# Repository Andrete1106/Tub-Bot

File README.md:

# Proyecto Tub-Bot
Repositorio para el Proyecto "Tub-Bot" correspondiente a las materias de:
- Introducción a Ingeniería Electrónica 
- Taller de Electrónica

**Universidad Nacional de Colombia**

## **Integrantes**
- Andres David Hincapié Álvarez (Ingeniería Electrónica)  
- Samuel Alejandro Bulla Fiquitiva (Ingeniería Electrónica)
- Juan Jose Aleman Martinez (Ingeniería Electrónica)
- Camilo Andrés Triana Ortiz (Ingeniería Mecatrónica)
- Ricardo Javier Rivas Sabogal (Ingeniería Electrónica)
- Luis Armando Berrocal Estrada (Ingeniería Electrónica)

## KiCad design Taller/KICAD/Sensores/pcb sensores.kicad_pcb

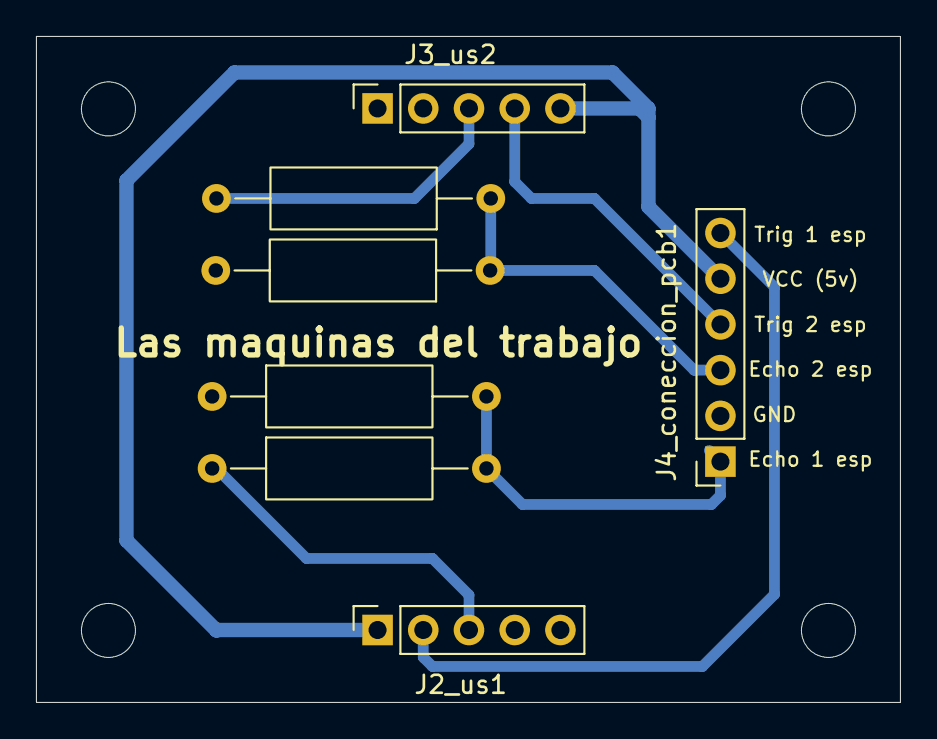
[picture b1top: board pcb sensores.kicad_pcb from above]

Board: 2 copper layers, 48.0 x 37.0 mm, 7 parts (0 on the bottom side), 8 nets.

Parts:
J2_us1, J3_us2: Conn_01x05; PinSocket_1x05_P2.54mm_Vertical
J4_coneccion_pcb1: Conn_01x06; PinSocket_1x06_P2.54mm_Vertical
R1, R4: 20 KOhm; R_Axial_DIN0309_L9.0mm_D3.2mm_P15.24mm_Horizontal
R2, R3: 10 KOhm; R_Axial_DIN0309_L9.0mm_D3.2mm_P15.24mm_Horizontal

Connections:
+5V: J2_us1.1 (vcc_us1), J3_us2.5 (vcc_us2), J4_coneccion_pcb1.5
/echo1_esp: J4_coneccion_pcb1.1, R1.2, R2.2
/echo2_esp: J4_coneccion_pcb1.3, R3.1, R4.1
/trig1_esp: J2_us1.2 (trig1_raw), J4_coneccion_pcb1.6
/trig2_esp: J3_us2.4 (trig2_raw), J4_coneccion_pcb1.4
GND: J2_us1.5 (GND_us1), J3_us2.1 (GND_us2), J4_coneccion_pcb1.2, R1.1, R4.2
unnamed: J2_us1.3 (echo1_raw), R2.1
unnamed: J3_us2.3 (echo2_raw), R3.2

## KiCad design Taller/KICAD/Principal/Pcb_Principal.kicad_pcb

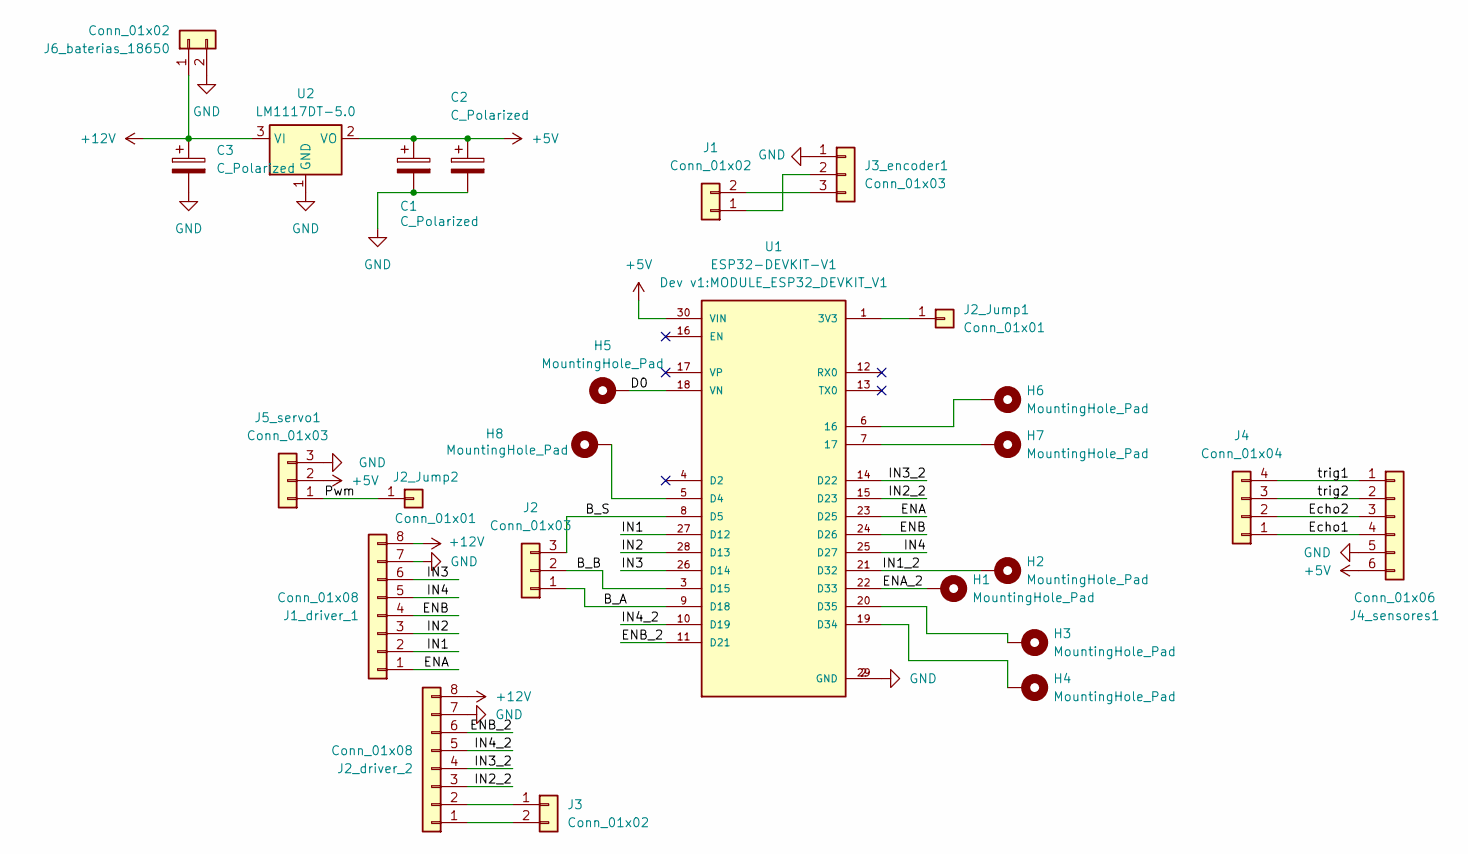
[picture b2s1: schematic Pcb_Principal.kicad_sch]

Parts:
C1, C2, C3: C_Polarized; CP_Radial_D5.0mm_P2.50mm
H1, H2, H3, H4, H5, H6, H7, H8: MountingHole_Pad; Pin_D1.0mm_L10.0mm
J1, J3: Conn_01x02; PinHeader_1x02_P2.54mm_Vertical
J1_driver_1, J2_driver_2: Conn_01x08; PinSocket_1x08_P2.54mm_Vertical
J2: Conn_01x03; PinHeader_1x03_P2.54mm_Vertical
J2_Jump1, J2_Jump2: Conn_01x01; PinHeader_1x01_P2.54mm_Vertical
J3_encoder1, J5_servo1: Conn_01x03; PinSocket_1x03_P2.54mm_Vertical
J4: Conn_01x04; PinHeader_1x04_P2.54mm_Vertical
J4_sensores1: Conn_01x06; PinSocket_1x06_P2.54mm_Vertical
J6_baterias_18650: Conn_01x02; PinSocket_1x02_P2.54mm_Vertical
U1: ESP32-DEVKIT-V1; MODULE_ESP32_DEVKIT_V1; PARTREV N/A
U2: LM1117DT-5.0; SIPAK_Vertical

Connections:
+5V: C1.1, C2.1, J4_sensores1.6 (s), J5_servo1.2, U1.30 (VIN), U2.2 (VO)
+12V: C3.1, J1_driver_1.8 (+12V), J2_driver_2.8 (+12V), J6_baterias_18650.1, U2.3 (VI)
/B_A: J2.1, U1.9 (D18)
/B_B: J2.2, U1.3 (D15)
/B_S: J2.3, U1.8 (D5)
/D0: H5.1, U1.18 (VN)
/ENA: J1_driver_1.1 (ENA), U1.23 (D25)
/ENA_2: H1.1, U1.22 (D33)
/ENB: J1_driver_1.4 (IN3), U1.24 (D26)
/ENB_2: J2_driver_2.6 (ENB), U1.11 (D21)
/Echo1: J4.1, J4_sensores1.4
/Echo2: J4.2, J4_sensores1.3
/IN1: J1_driver_1.2 (IN1), U1.27 (D12)
/IN1_2: H2.1, U1.21 (D32)
/IN2: J1_driver_1.3 (IN2), U1.28 (D13)
/IN2_2: J2_driver_2.3 (IN2_2), U1.15 (D23)
/IN3: J1_driver_1.6 (ENB), U1.26 (D14)
/IN3_2: J2_driver_2.4 (IN3), U1.14 (D22)
/IN4: J1_driver_1.5 (IN4), U1.25 (D27)
/IN4_2: J2_driver_2.5 (IN4), U1.10 (D19)
/Pwm: J2_Jump2.1, J5_servo1.1
/trig1: J4.4, J4_sensores1.1
/trig2: J4.3, J4_sensores1.2 (trig2)
GND: C1.2, C2.2, C3.2, J1_driver_1.7 (GND), J2_driver_2.7 (GND), J3_encoder1.1, J4_sensores1.5, J5_servo1.3, J6_baterias_18650.2, U1.2 (GND), U1.29 (GND), U2.1 (GND)
unnamed: J1.1, J3_encoder1.2
unnamed: J1.2, J3_encoder1.3
unnamed: J2_Jump1.1, U1.1 (3V3)
unnamed: J2_driver_2.1 (ENA), J3.2
unnamed: J2_driver_2.2 (IN1), J3.1
unnamed: H6.1, U1.6 (16)
unnamed: H7.1, U1.7 (17)
unnamed: H8.1, U1.5 (D4)
unnamed: H4.1, U1.19 (D34)
unnamed: H3.1, U1.20 (D35)

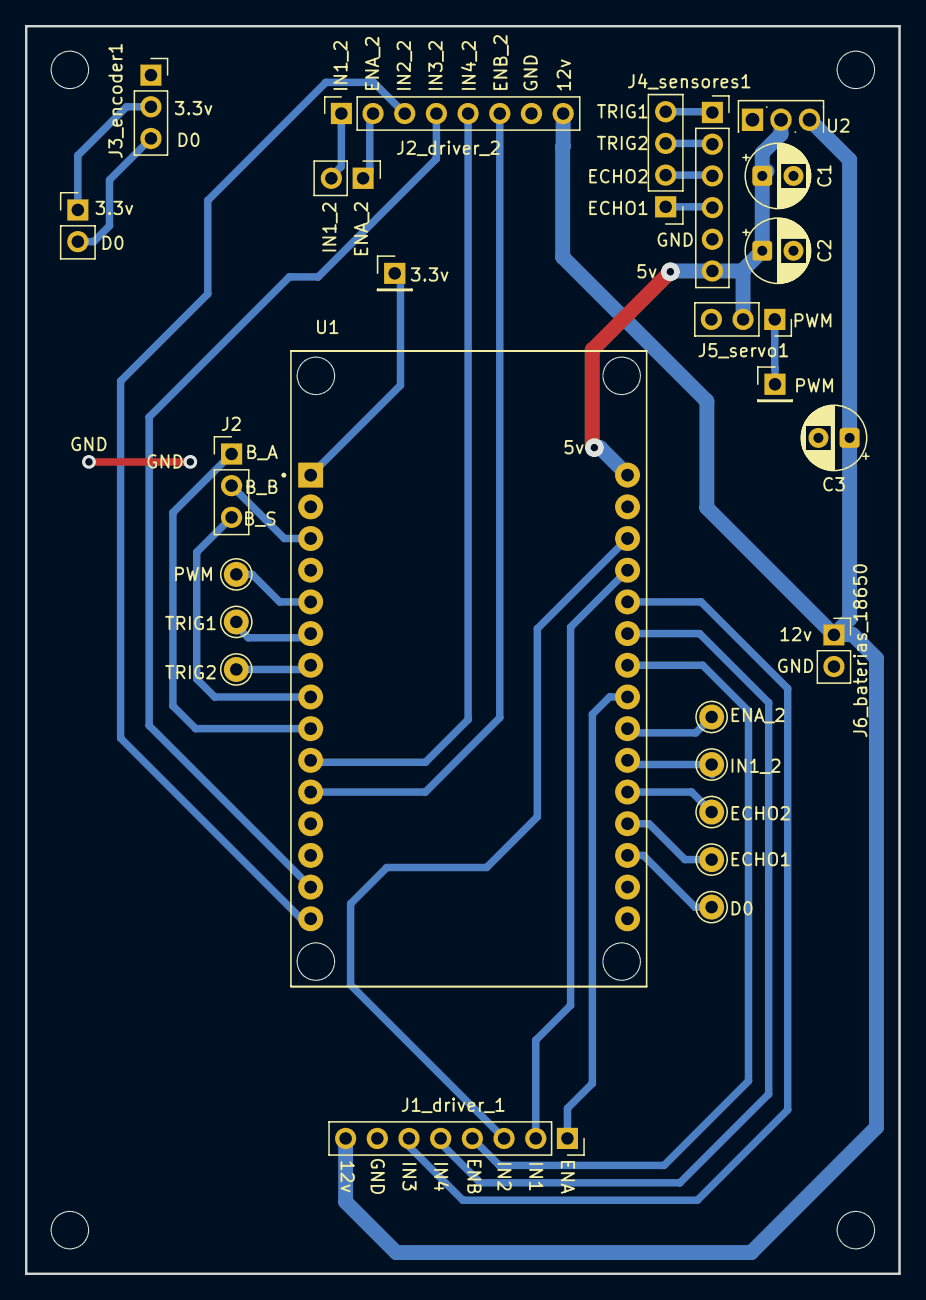
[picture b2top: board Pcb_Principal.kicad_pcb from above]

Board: 2 copper layers, 70.0 x 100.0 mm, 25 parts (0 on the bottom side), 34 nets.

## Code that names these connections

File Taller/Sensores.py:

from machine import Pin, PWM
from machine import Pin, time_pulse_us
import time


# === Pines del Sensor 1 ===
TRIG1 = Pin(16, Pin.OUT)
ECHO1 = Pin(34, Pin.IN)

# === Pines del Sensor 2 ===
TRIG2 = Pin(17, Pin.OUT)
ECHO2 = Pin(35, Pin.IN)

# Pin donde conectar la señal del servo
servo = PWM(Pin(4), freq=50)

# Función genérica para medir distancia en un sensor
def medir_distancia(TRIG, ECHO):
    # Asegurar TRIG en LOW
    TRIG.value(0)
    time.sleep_us(5)

    # Enviar pulso
    TRIG.value(1)
    time.sleep_us(10)
    TRIG.value(0)

    # Medir tiempo del pulso en ECHO
    duracion = time_pulse_us(ECHO, 1, 30000)

    if duracion < 0:
        return None

    distancia = (duracion / 2) * 0.343
    return distancia
# Conversión de grados a duty_us (microsegundos)
def set_angle(angle):
    # MG90S normalmente usa 500-2400 us
    min_us = 500
    max_us = 2400
    us = min_us + (angle / 180) * (max_us - min_us)
    servo.duty_u16(int(us * 65535 / 20000))  # 20 ms period
    time.sleep(0.02)
set_angle(0)
print("servo en angulo 0")
time.sleep(5)

def Show_SensorU():
    #Sensor 1
    d1 = medir_distancia(TRIG1, ECHO1)
    time.sleep_ms(20)  # pequeño delay para evitar interferencias

    #Sensor 2
    d2 = medir_distancia(TRIG2, ECHO2)
    time.sleep_ms(10)
    
    print("Sensor 1:", "Sin lectura" if d1 is None else f"{round(d1,2)} mm")
    print("Sensor 2:", "Sin lectura" if d2 is None else f"{round(d2,2)} mm")
    time.sleep(0.1)
# Movimiento de prueba
while True:
    for ang in range(0, 201, 5):
        set_angle(ang)
        time.sleep(0.02)
        Show_SensorU()
        print(ang)

    for ang in range(200, -1, -5):
        set_angle(ang)
        time.sleep(0.02)
        Show_SensorU()
        print(ang)

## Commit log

2025-11-24 Create a
2025-11-24 Create Fractales
2025-11-24 Create c
2025-11-24 Create h
2025-11-24 Create j
2025-12-04 Create ab
2025-12-04 Create Borrar
2025-12-13 Replace content in Hola file
2025-12-13 Update and rename Hola to Borrar
